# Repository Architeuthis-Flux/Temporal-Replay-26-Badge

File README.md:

# Temporal Badge

Conference badge for Temporal's events. ESP32-S3-MINI-1 (XIAO form factor) with SSD1309
OLED, IR TX/RX for attendee pairing, joystick, tilt switch, and NVS-backed identity.

## Hardware

- **MCU**: ESP32-S3 16r8, dual-core Xtensa LX7, 8 MB flash
- **Display**: SSD1309 128×64 OLED via hardware I2C (SDA=D4/GPIO5, SCL=D5/GPIO6)
- **IR**: NEC protocol TX (D2/GPIO3) + RX (D3/GPIO4)
- **Input**: 4 buttons (D7–D10), analog joystick (D0/D1), tilt switch (D6)

## Prerequisites

- Python 3.9+
- All other dependencies (PlatformIO, Temporal CLI, esptool) are installed by `ignition/setup.sh`

## Build & Flash (Ignition)

```bash
cd ignition
./setup.sh        # first time only — installs all dependencies
./start.sh        # build + flash all connected badges
./start.sh --build-and-flash  # explicit build + fresh filesystem + flash
./start.sh -y     # skip the pre-flash Enter prompt for a ready batch
```

Ignition treats each run as one connected hub batch. Temporal starts a parent
`FlashBadgesWorkflow` plus one human-readable `BadgeFlashWorkflow` child per
detected badge, so the UI shows per-badge flash/WiFi progress and results.

See [`ignition/README.md`](ignition/README.md) for full usage, including `--no-build`, `--build-only`, and `--firmware-dir` options.

## Build (Firmware)

```bash
cd firmware

# Echo badge (default)
./build.sh

# Charlie board
./build.sh charlie

# Non-interactive build (skip build-time network prompt)
./build.sh echo -n
```

Or directly via PlatformIO:
```bash
pio run -e echo
pio run -e charlie
```
Direct PlatformIO builds read `firmware/wifi.local.env` or `BADGE_*`
environment variables and fail if WiFi credentials or the server URL are
missing.

### Dev menu build

Normal firmware hides internal debug/test screens. To flash an Echo badge with
the dev menu enabled for diagnostics and badge-info editing:

```bash
cd firmware
pio run -e echo-dev -t upload --upload-port /dev/cu.usbmodem1101
```

`echo-dev` still uses the configured boop API; it only changes menu/debug
visibility. Use a local settings/server override if you need to avoid staging.

Normal firmware boots straight into the badge menu. Production builds show
Boop, Messages, Contacts, New Msg, Settings, and QR / Pair only while the
badge is unpaired; debug/test screens stay behind the dev menu build.

### MicroPython apps

MicroPython app source lives in `firmware/initial_filesystem/apps/` and is
embedded into firmware builds through `firmware/scripts/generate_startup_files.py`.
Use folder apps with a `main.py` entry point for anything larger than a demo.

Normal firmware does not show the generic Apps menu. Attendee-facing
MicroPython apps need a native `GUI.cpp` launcher and icon; diagnostics can
stay in the dev-menu Apps browser. See
[`firmware/initial_filesystem/apps/README.md`](firmware/initial_filesystem/apps/README.md)
for the full authoring, validation, and build workflow.

### Serial logging

To capture logs from every connected badge while testing hardware flows:

```bash
cd firmware
~/.platformio/penv/bin/python serial_log.py
```

The logger auto-detects USB serial ports, clears `firmware/logs/` by default,
and writes one log file per badge.

### Two-badge hardware test harness

The planned firmware hardware harness uses Ignition to build/flash two badges,
then drives them over USB serial for physical boop and clean-state tests.
See [`docs/hardware-test-harness.md`](docs/hardware-test-harness.md) and
[`specs/012-hardware-test-harness/tasks.md`](specs/012-hardware-test-harness/tasks.md).

## Power Management

The badge uses a 1000 mAh battery drawing ~10 mA in normal operation (~100 hours).
Power saving is tuned for multi-day conferences where WiFi reconnects (~400 mA
for several seconds) cost more than the deep sleep saves if triggered too often.

| State | Trigger | What happens |
|-------|---------|--------------|
| **Active** | Motion / button press | Full brightness, WiFi connected |
| **Dim** | 5 min no motion | LED matrix dims to brightness 3, WiFi stays connected |
| **Deep sleep** | 20 min no motion | 12 μA draw, WiFi disconnects, wakes on IMU motion |
| **Deep sleep (unpaired)** | 5 min no motion | Unpaired badges sleep sooner to save battery in storage |
| **Force sleep** | Hold **UP** button 5 seconds | Immediately enters deep sleep (disabled over USB) |

To wake from deep sleep, move or tilt the badge. After waking, WiFi reconnects
automatically.

## Configuration

Display, input, boop, and timing settings live in `settings.txt` on the
badge's FAT filesystem — no recompile needed. WiFi credentials and the server
URL are build-time secrets and are not written to the badge filesystem.

To configure a badge:
1. Copy `firmware/wifi.local.env.example` to `firmware/wifi.local.env`:
```
BADGE_WIFI_SSID=YourNetwork
BADGE_WIFI_PASS=YourPassword
BADGE_SERVER_URL=https://your-server.example.com
```
2. Build/flash from `firmware/`; the build embeds those values into the firmware.
3. Edit non-secret settings in `settings.txt` as needed:
```
[wifi]
ep_badge = /api/v1/badge
ep_boops = /api/v1/boops
```

`firmware/wifi.local.env` is ignored by git. Environment variables with the
same names override that file for one-off builds. Changing WiFi or backend URL
now requires rebuilding and reflashing the firmware.
Builds require `BADGE_WIFI_SSID`, `BADGE_WIFI_PASS`, and `BADGE_SERVER_URL`;
the badge depends on API connectivity for pairing, messaging, and schedule data.
Badge-facing API calls use MessagePack where supported. Schedule data uses a
compact MessagePack schema and is cached on-device with ETag sidecars. The
schedule app supports `MINE` and `ALL` modes, refreshes in the background on
open, and shows a ticket-page QR for editing an attendee's custom schedule.
Boop and ping list reads also use compact MessagePack arrays; see
[`firmware/src/README.md`](firmware/src/README.md#backend-wire-format) for the
wire contract and measured payload savings.

## Pairing QR

The on-device QR code encodes the badge's compact 12-character machine id,
uppercased for QR alphanumeric mode. The registration scanner uses that id to
attach the physical badge to an attendee record and the badge then fetches the
server-owned identity data.

## Serial Monitor

```bash
cd firmware
pio device monitor --port /dev/cu.usbmodem114101 --baud 115200
```

Or use `./flash.py` (default behavior) to flash and then auto-open monitor logs for one badge.

## Hardware Targets

| Target | Board | Defines file |
|--------|-------|------|
| `delta` | Temporal Badge DELTA (ESP32-S3-MINI-1, XIAO form factor) | `firmware/src/DeltaDefines.h` |
| `charlie` | Jumperless/Charlie board (ESP32-S3-DevKitC-1-N16R8V) | `firmware/src/CharlieDefines.h` |
| `echo` | Echo board production firmware | `firmware/src/EchoDefines.h` |
| `echo-dev` | Echo board with internal dev menu enabled | `firmware/src/EchoDefines.h` |

### Adding a new hardware target

1. Copy `firmware/src/DeltaDefines.h` → `firmware/src/MyBoardDefines.h`
2. Update pin numbers to match your schematic
3. Add `BADGE_HAS_*` flags for any optional peripherals your board has (see `firmware/src/CharlieDefines.h` for the full list)
4. Add a new `[env:myboard]` section to `firmware/platformio.ini` with `-DHARDWARE_MYBOARD`
5. Add `#include "MyBoardDefines.h"` to `firmware/src/HardwareConfig.h`

## Key Source Files

- [firmware/src/main.cpp](firmware/src/main.cpp) — setup() and loop()
- [firmware/src/HardwareConfig.h](firmware/src/HardwareConfig.h) — hardware target selector
- [firmware/src/DeltaDefines.h](firmware/src/DeltaDefines.h) — DELTA pin assignments
- [firmware/src/CharlieDefines.h](firmware/src/CharlieDefines.h) — Charlie pin assignments + feature flags
- [firmware/platformio.ini](firmware/platformio.ini) — build environments

## Repo Structure

| Directory | Contents |
|-----------|----------|
| [`firmware/`](firmware/) | Arduino C++ firmware — active PlatformIO project |
| [`hardware/DELTA/`](hardware/DELTA/) | KiCad PCB — ESP32-S3-MINI-1 XIAO, SSD1309 OLED, IR, buttons |
| [`registrationScanner/`](registrationScanner/) | Quart + Temporal backend (badge enrollment + boop workflows) |
| [`specs/`](specs/) | Feature specs and implementation plans |
| [`assets/`](assets/) | Art and design resources |
| [`docs/`](docs/) | Design notes, photos, work log |

## Legacy Firmware

`firmware/Firmware-0308-modular/` and `firmware/Firmware-0308/` are previous Arduino IDE builds kept for reference. They use a different build system and are not maintained.

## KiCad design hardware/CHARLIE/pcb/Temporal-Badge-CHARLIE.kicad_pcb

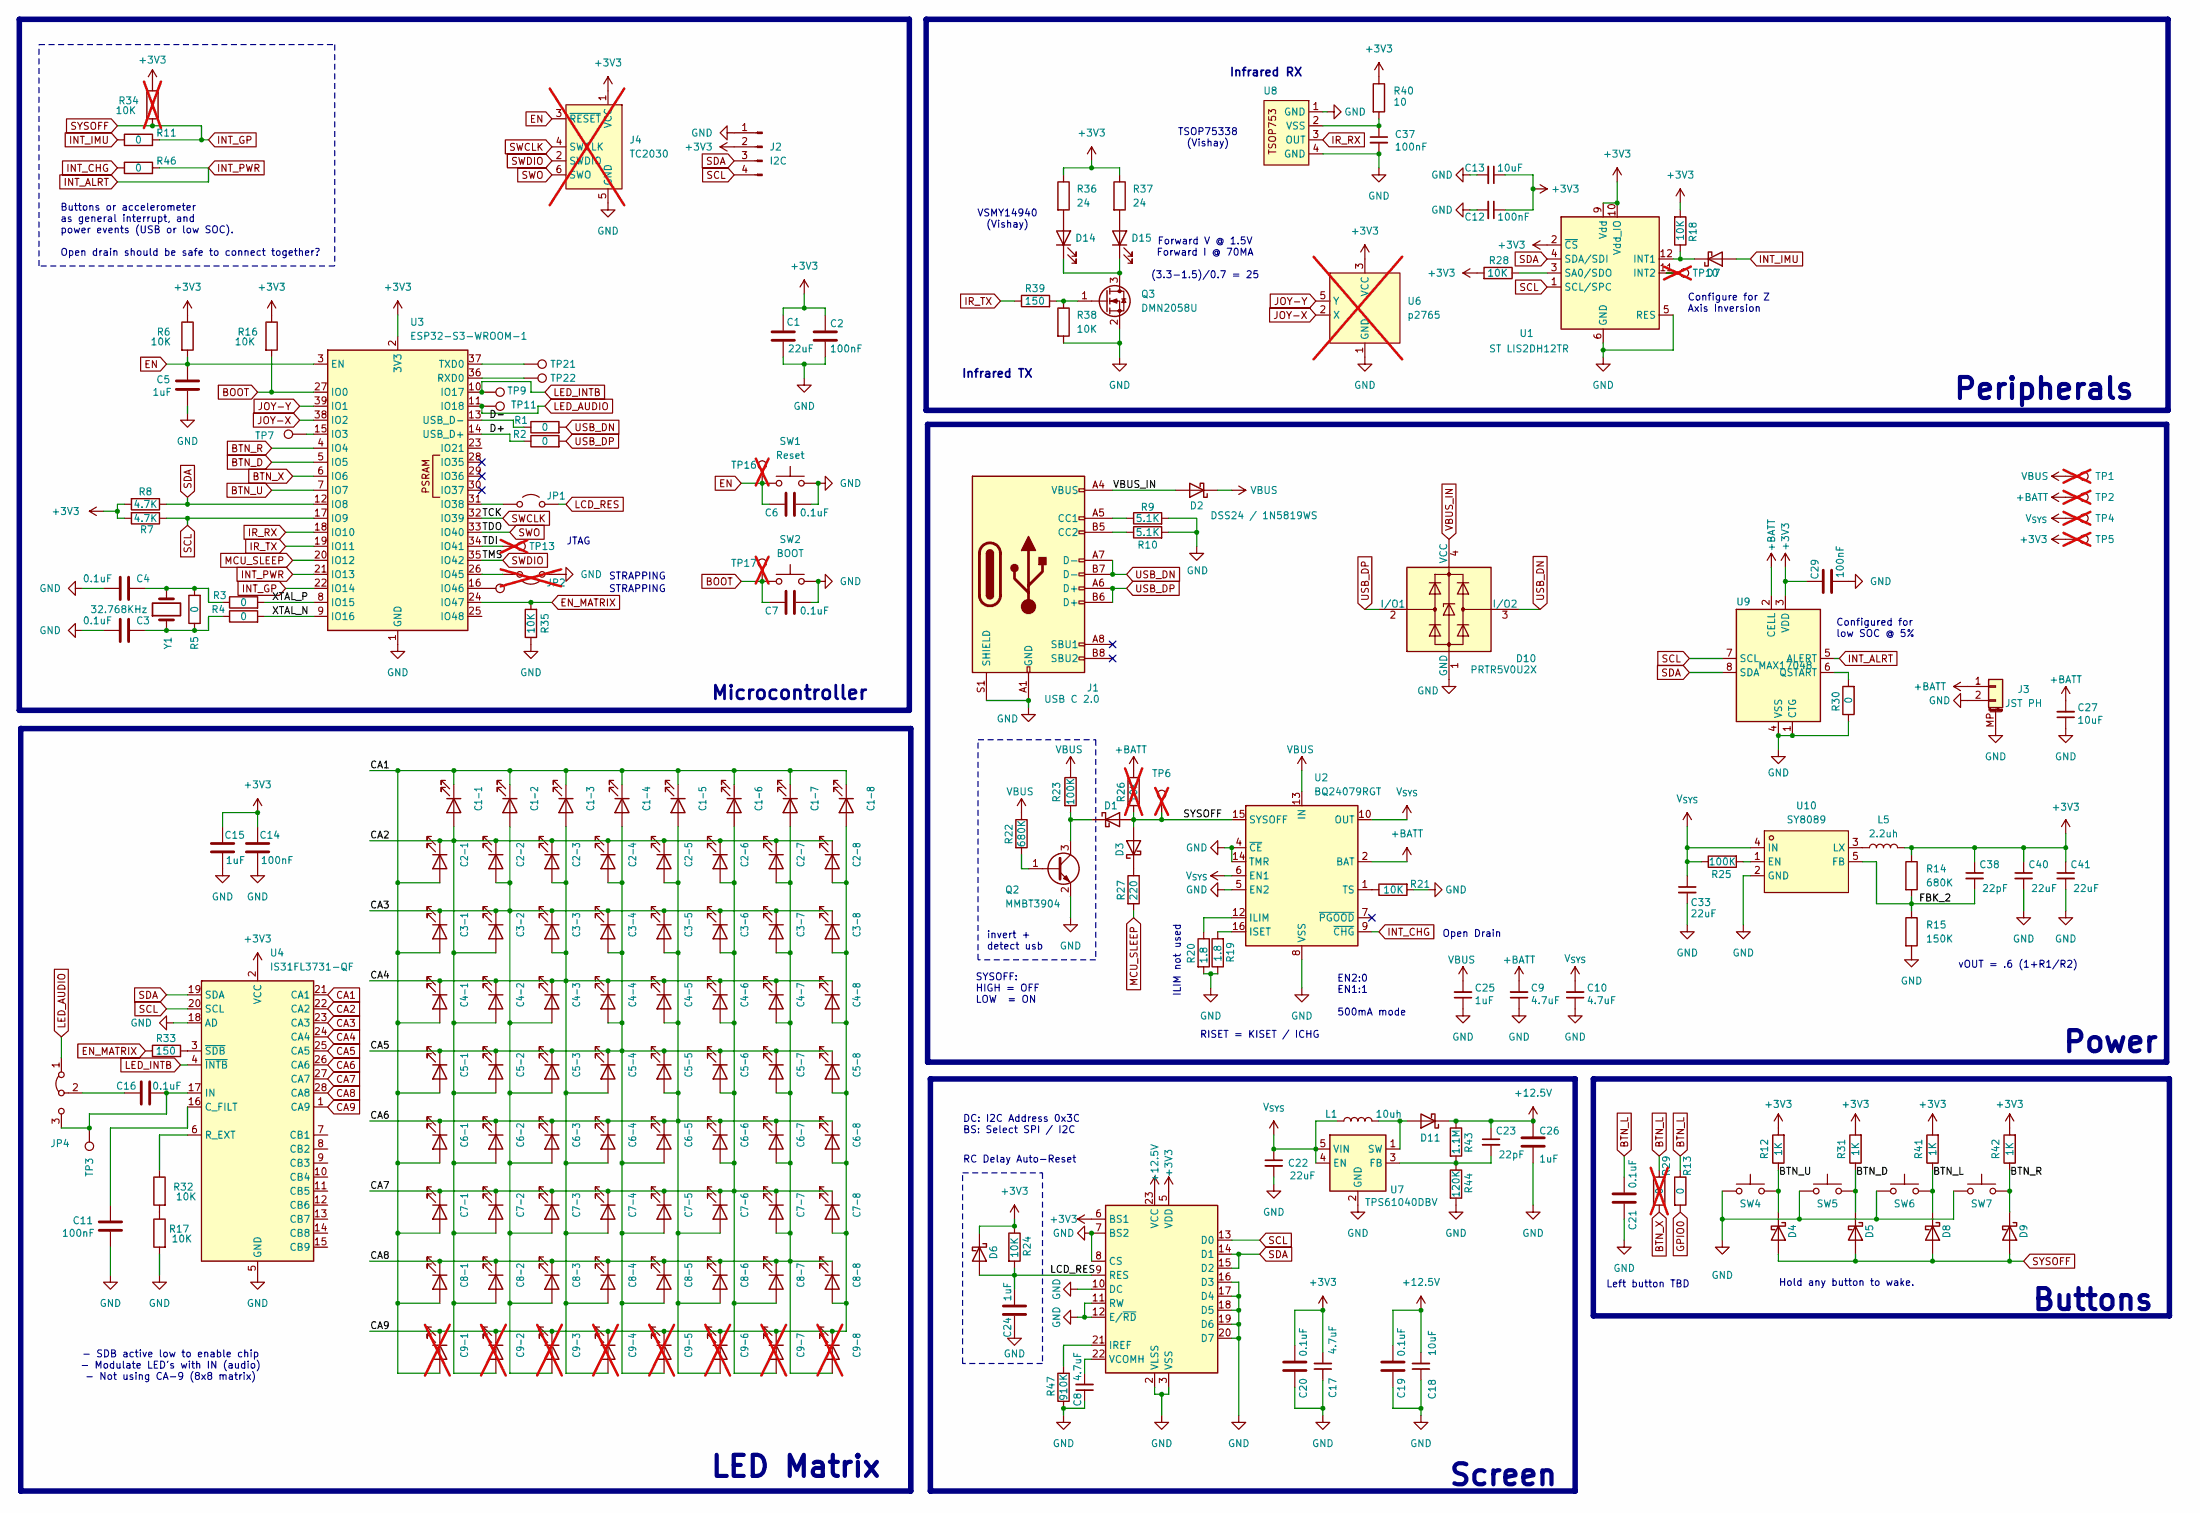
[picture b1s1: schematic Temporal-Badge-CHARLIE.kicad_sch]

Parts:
C1, C22, C33, C40, C41: 22uF; C_0402_1005Metric; LCSC C3845593
C1-1, C1-2, C1-3, C1-4, C1-5, C1-6, C1-7, C1-8, C2-1, C2-2, C2-3, C2-4, C2-5, C2-6, C2-7, C2-8, C3-1, C3-2, C3-3, C3-4, C3-5, C3-6, C3-7, C3-8, C4-1, C4-2, C4-3, C4-4, C4-5, C4-6, C4-7, C4-8, C5-1, C5-2, C5-3, C5-4, C5-5, C5-6, C5-7, C5-8, C6-1, C6-2, C6-3, C6-4, C6-5, C6-6, C6-7, C6-8, C7-1, C7-2, C7-3, C7-4, C7-5, C7-6, C7-7, C7-8, C8-1, C8-2, C8-3, C8-4, C8-5, C8-6, C8-7, C8-8: LED0603_NOOUTLINE; CHIPLED_0603_NOOUTLINE; LCSC C19171390
C2, C11, C12, C14, C29, C37: 100nF; C_0402_1005Metric; LCSC C1525
C3, C4, C6, C7, C16, C19, C20, C21: 0.1uF; C_0402_1005Metric; LCSC C1525
C5, C15, C24, C25: 1uF; C_0402_1005Metric; LCSC C14445
C8, C9, C10, C17: 4.7uF; C_0402_1005Metric; LCSC C315248
C9-1, C9-2, C9-3, C9-4, C9-5, C9-6, C9-7, C9-8: LED0603_NOOUTLINE; CHIPLED_0603_NOOUTLINE; not fitted
C13, C18, C27: 10uF; C_0402_1005Metric; LCSC C315248
C23, C38: 22pF; C_0402_1005Metric; LCSC C76960
C26: 1uF; C_0402_1005Metric; LCSC C1525
D1, D3, D4, D5, D6, D7, D8, D9, D11: D_Schottky; D_SOD-523; LCSC C917006
D2: DSS24 / 1N5819WS; D_SOD-123F; LCSC C511865
D10: PRTR5V0U2X; SOT-143; LCSC C5180302
D14, D15: VSMY14940; vsmy14940; LCSC C511069
J1: USB C 2.0; USB_C_Receptacle_Palconn_UTC16-G; LCSC C2765186
J2: I2C; PinSocket_1x04_P2.54mm_Vertical
J3: JST PH; JST_PH_S2B-PH-SM4-TB_1x02-1MP_P2.00mm_Horizontal; LCSC C295747
J4: TC2030; Tag-Connect_TC2030-IDC-NL_2x03_P1.27mm_Vertical; not fitted
JP1: Jumper_2_Open; SolderJumper-2_P1.3mm_Open_RoundedPad1.0x1.5mm
JP2: Jumper_2_Open; SolderJumper-2_P1.3mm_Open_RoundedPad1.0x1.5mm; not fitted
JP4: Jumper_3_Bridged12; SolderJumper-3_P1.3mm_Bridged12_Pad1.0x1.5mm
L1: 10uh; L_Coilcraft_LPS3010; LCSC C2926400
L5: 2.2uh; L_Coilcraft_LPS3010; LCSC C2926400
Q2: MMBT3904; SOT-23; LCSC C916374
Q3: DMN2058U; SOT-23; LCSC C461001
R1, R2, R3, R4, R5, R11, R13, R30, R46: 0; R_0201_0603Metric; LCSC C106228
R6, R16, R17, R18, R21, R24, R28, R32, R35, R38: 10K; R_0402_1005Metric; LCSC C60490
R7, R8: 4.7K; R_0402_1005Metric; LCSC C105871
R9, R10: 5.1K; R_0402_1005Metric; LCSC C25905
R12, R31, R41, R42: 1K; R_0402_1005Metric; LCSC C106235
R14, R22: 680K; R_0402_1005Metric; LCSC C163456
R15: 150K; R_0402_1005Metric; LCSC C93947
R19, R20: 1.8; R_0402_1005Metric; LCSC C203083
R23, R25: 100K; R_0402_1005Metric; LCSC C60491
R26: 10K; R_0402_1005Metric; LCSC C25767; not fitted
R27: 220; R_0402_1005Metric; LCSC C112291
R29: 0; R_0201_0603Metric; LCSC C106228; not fitted
R33, R39: 150; R_0402_1005Metric; LCSC C138054
R34: 10K; R_0402_1005Metric; LCSC C60490; not fitted
R36, R37: 24; R_0805_2012Metric; LCSC C270625
R40: 10; R_0402_1005Metric; LCSC C138066
R43: 1.1M; R_0402_1005Metric; LCSC C163456
R44: 120K; R_0402_1005Metric; LCSC C93947
R47: 910K; R_0402_1005Metric; LCSC C163456
SW1: Reset; SW_SPST_B3U-1000P-B; LCSC C231329
SW2: BOOT; Panasonic_EVQPUM_EVQPUD; LCSC C79174
SW4, SW5, SW6, SW7: SW_Push; SW_Push_1TS009xxxx-xxxx-xxxx_6x6x5mm; LCSC C25168849
TP1, TP2, TP4, TP5, TP6, TP10, TP13, TP16, TP17: TestPoint; TestPoint_Pad_D1.0mm; not fitted
TP3, TP7, TP8, TP9, TP11, TP21, TP22: TestPoint; TestPoint_Pad_D1.0mm
U1: ST LIS2DH12TR; LGA-12_2x2mm_P0.5mm; LCSC C110926
U2: BQ24079RGT; VQFN-16-1EP_3x3mm_P0.5mm_EP1.6x1.6mm; LCSC C2876751
U3: ESP32-S3-WROOM-1; LCSC C2913202
U4: IS31FL3731-QF; QFN-28-1EP_4x4mm_P0.4mm_EP2.3x2.3mm; LCSC C191206
U5: (no value)
U6: p2765; JOYSTICK_ANALOG_MINITHM; not fitted
U7: TPS61040DBV; SOT-23-5
U8: TSOP75338; TSOP753; LCSC C499550
U9: MAX17048; TDFN-8-1EP_2x2mm_P0.5mm_EP0.8x1.2mm; LCSC C2682616
U10: SY8089; SOT-23-5; LCSC Part C79313
Y1: 32.768KHz; Crystal_SMD_3215-2Pin_3.2x1.5mm; LCSC C97606

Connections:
+3V3: C1.1, C2.1, C12.1, C13.1, C14.1, C15.1, C17.2, C20.2, C29.1, C38.1, C40.1, C41.1, D6.1 (K), J2.2, J4.1 (VCC), L5.2, R6.1, R7.2, R8.2, R12.2, R14.1, R16.1, R18.2, R24.1, R28.2, R31.2, R34.1, R36.1, R37.1, R40.1, R41.2, R42.2, TP5.1, U1.2 (~CS), U1.9 (Vdd), U1.10 (Vdd_IO), U3.2 (3V3), U4.2 (VCC), U5.5 (VDD), U5.6 (BS1), U6.3 (VCC), U6.4 (VCC), U9.3 (VDD)
+12.5V: C18.2, C19.2, C23.1, C26.2, D11.1 (K), R43.1, U5.23 (VCC)
+BATT: C9.2, C27.2, J3.1, R26.1, TP2.1, U2.2 (BAT), U2.3 (BAT), U9.2 (CELL)
/D+: R2.1, U3.14 (USB_D+)
/D-: R1.1, U3.13 (USB_D-)
/FBK_2: C38.2, R14.2, R15.1, U10.5 (FB)
/TDI: TP13.1, U3.34 (IO41)
/XTAL_N: R4.2, U3.9 (IO16)
/XTAL_P: R3.2, U3.8 (IO15)
BOOT: C7.1, R16.2, SW2.2, TP17.1, U3.27 (IO0)
BTN_D: D5.1 (K), R31.1, SW5.2, U3.5 (IO5)
BTN_L: C21.2, D8.1 (K), R13.1, R29.1, R41.1, SW6.2
BTN_R: D9.1 (K), R42.1, SW7.2, U3.4 (IO4)
BTN_U: D4.1 (K), R12.1, SW4.2, U3.7 (IO7)
BTN_X: R29.2, U3.6 (IO6)
CA1: C1-1.1 (K), C1-2.1 (K), C1-3.1 (K), C1-4.1 (K), C1-5.1 (K), C1-6.1 (K), C1-7.1 (K), C1-8.1 (K), C2-1.2 (A), C3-1.2 (A), C4-1.2 (A), C5-1.2 (A), C6-1.2 (A), C7-1.2 (A), C8-1.2 (A), C9-1.2 (A), U4.21 (CA1)
CA2: C1-1.2 (A), C2-1.1 (K), C2-2.1 (K), C2-3.1 (K), C2-4.1 (K), C2-5.1 (K), C2-6.1 (K), C2-7.1 (K), C2-8.1 (K), C3-2.2 (A), C4-2.2 (A), C5-2.2 (A), C6-2.2 (A), C7-2.2 (A), C8-2.2 (A), C9-2.2 (A), U4.22 (CA2)
CA3: C1-2.2 (A), C2-2.2 (A), C3-1.1 (K), C3-2.1 (K), C3-3.1 (K), C3-4.1 (K), C3-5.1 (K), C3-6.1 (K), C3-7.1 (K), C3-8.1 (K), C4-3.2 (A), C5-3.2 (A), C6-3.2 (A), C7-3.2 (A), C8-3.2 (A), C9-3.2 (A), U4.23 (CA3)
CA4: C1-3.2 (A), C2-3.2 (A), C3-3.2 (A), C4-1.1 (K), C4-2.1 (K), C4-3.1 (K), C4-4.1 (K), C4-5.1 (K), C4-6.1 (K), C4-7.1 (K), C4-8.1 (K), C5-4.2 (A), C6-4.2 (A), C7-4.2 (A), C8-4.2 (A), C9-4.2 (A), U4.24 (CA4)
CA5: C1-4.2 (A), C2-4.2 (A), C3-4.2 (A), C4-4.2 (A), C5-1.1 (K), C5-2.1 (K), C5-3.1 (K), C5-4.1 (K), C5-5.1 (K), C5-6.1 (K), C5-7.1 (K), C5-8.1 (K), C6-5.2 (A), C7-5.2 (A), C8-5.2 (A), C9-5.2 (A), U4.25 (CA5)
CA6: C1-5.2 (A), C2-5.2 (A), C3-5.2 (A), C4-5.2 (A), C5-5.2 (A), C6-1.1 (K), C6-2.1 (K), C6-3.1 (K), C6-4.1 (K), C6-5.1 (K), C6-6.1 (K), C6-7.1 (K), C6-8.1 (K), C7-6.2 (A), C8-6.2 (A), C9-6.2 (A), U4.26 (CA6)
CA7: C1-6.2 (A), C2-6.2 (A), C3-6.2 (A), C4-6.2 (A), C5-6.2 (A), C6-6.2 (A), C7-1.1 (K), C7-2.1 (K), C7-3.1 (K), C7-4.1 (K), C7-5.1 (K), C7-6.1 (K), C7-7.1 (K), C7-8.1 (K), C8-7.2 (A), C9-7.2 (A), U4.27 (CA7)
CA8: C1-7.2 (A), C2-7.2 (A), C3-7.2 (A), C4-7.2 (A), C5-7.2 (A), C6-7.2 (A), C7-7.2 (A), C8-1.1 (K), C8-2.1 (K), C8-3.1 (K), C8-4.1 (K), C8-5.1 (K), C8-6.1 (K), C8-7.1 (K), C8-8.1 (K), C9-8.2 (A), U4.28 (CA8)
CA9: C1-8.2 (A), C2-8.2 (A), C3-8.2 (A), C4-8.2 (A), C5-8.2 (A), C6-8.2 (A), C7-8.2 (A), C8-8.2 (A), C9-1.1 (K), C9-2.1 (K), C9-3.1 (K), C9-4.1 (K), C9-5.1 (K), C9-6.1 (K), C9-7.1 (K), C9-8.1 (K), U4.1 (CA9)
EN: C5.1, C6.1, J4.3 (~RESET), R6.2, SW1.2, TP16.1, U3.3 (EN)
EN_MATRIX: R33.1, R35.2, U3.24 (IO47)
GND: C1.2, C2.2, C3.2, C4.2, C5.2, C6.2, C7.2, C8.1, C9.1, C10.1, C11.2, C12.2, C13.2, C14.2, C15.2, C17.1, C18.1, C19.1, C20.1, C21.1, C22.2, C24.2, C25.1, C26.1, C27.1, C29.2, C33.2, C37.2, C40.2, C41.2, D10.1 (GND), J1.A1 (GND), J1.A12 (GND), J1.B1 (GND), J1.B12 (GND), J1.S1 (SHIELD), J2.1, J3.2, J3.MP (MountPin), J4.5 (GND), JP2.2 (B), Q2.2 (E), Q3.2 (S), R9.2, R10.2, R15.2, R17.2, R19.1, R20.2, R21.2, R30.1, R35.1, R38.2, R44.2, R47.1, SW1.1, SW2.1, SW4.1, SW5.1, SW6.1, SW7.1, U1.5 (RES), U1.6 (GND), U1.7 (GND), U1.8 (GND), U2.4 (~CE), U2.5 (EN2), U2.8 (VSS), U2.14 (TMR), U2.17 (VSS), U3.1 (GND), U3.40 (GND), U3.41 (GND), U4.5 (GND), U4.18 (AD), U4.29 (GND), U5.1 (NC), U5.2 (VLSS), U5.3 (VSS), U5.4 (NC), U5.7 (BS2), U5.8 (CS), U5.10 (DC), U5.11 (RW), U5.12 (E/~RD), U5.16 (D3), U5.17 (D4), U5.18 (D5), U5.19 (D6), U5.20 (D7), U5.24 (NC), U6.1 (GND), U6.6 (GND), U7.2 (GND), U8.1 (GND), U8.4 (GND), U9.1 (CTG), U9.4 (VSS), U9.9 (VSS), U10.2 (GND)
GPIO0: R13.2
INT_ALRT: R46.2, U3.21 (IO13), U9.5 (ALERT)
INT_CHG: R46.1, U2.9 (~CHG)
INT_GP: D1.2 (A), D3.2 (A), D4.2 (A), D5.2 (A), D8.2 (A), D9.2 (A), R11.2, R26.2, R34.2, TP6.1, U2.15 (SYSOFF), U3.22 (IO14)
INT_IMU: D7.2 (A), R11.1
IR_RX: U3.18 (IO10), U8.3 (OUT)
IR_TX: R39.1, U3.19 (IO11)
JOY-X: U3.38 (IO2), U6.2 (X)
JOY-Y: U3.39 (IO1), U6.5 (Y)
LCD_RES: C24.1, D6.2 (A), JP1.2 (B), R24.2, U5.9 (RES)
LED_AUDIO: JP4.1 (A), TP11.1, U3.11 (IO18)
LED_INTB: TP9.1, U3.10 (IO17), U4.4 (~INTB)
MCU_SLEEP: R27.2, U3.20 (IO12)
unnamed: C3.1, R4.1, R5.1, Y1.1
unnamed: C4.1, R3.1, R5.2, Y1.2
unnamed: D1.1 (K), Q2.3 (C), R23.2
unnamed: D3.1 (K), R27.1
unnamed: D7.1 (K), R18.1, U1.12 (INT1)
unnamed: D11.2 (A), L1.2, U7.1 (SW)
unnamed: D14.2 (A), R36.2
unnamed: D14.1 (K), D15.1 (K), Q3.3 (D)
unnamed: D15.2 (A), R37.2
unnamed: J1.A5 (CC1), R9.1
unnamed: J1.B5 (CC2), R10.1
unnamed: JP1.1 (A), U3.31 (IO38)
unnamed: JP2.1 (A), U3.26 (IO45)
unnamed: C16.2, JP4.3 (B), TP3.1, U4.17 (IN)
unnamed: C16.1, JP4.2 (C)
unnamed: Q2.1 (B), R22.2
unnamed: Q3.1 (G), R38.1, R39.2
unnamed: R17.1, R32.2
unnamed: TP10.1, U1.11 (INT2)
unnamed: R28.1, U1.3 (SA0/SDO)
unnamed: R20.1, U2.12 (ILIM)
unnamed: R19.2, U2.16 (ISET)
unnamed: R21.1, U2.1 (TS)
unnamed: TP7.1, U3.15 (IO3)
unnamed: TP8.1, U3.16 (IO46)
unnamed: TP22.1, U3.36 (RXD0)
unnamed: TP21.1, U3.37 (TXD0)
unnamed: C11.1, U4.16 (C_FILT)
unnamed: R32.1, U4.6 (R_EXT)
unnamed: R33.2, U4.3 (~SDB)
unnamed: R47.2, U5.21 (IREF)
unnamed: C8.2, U5.22 (VCOMH)
unnamed: C23.2, R43.2, R44.1, U7.3 (FB)
unnamed: C37.1, R40.2, U8.2 (VSS)
unnamed: R30.2, U9.6 (QSTART)
unnamed: R25.2, U10.1 (EN)
unnamed: L5.1, U10.3 (LX)
SCL: J2.4, R7.1, U1.1 (SCL/SPC), U3.17 (IO9), U4.20 (SCL), U5.13 (D0), U9.7 (SCL)
SDA: J2.3, R8.1, U1.4 (SDA/SDI), U3.12 (IO8), U4.19 (SDA), U5.14 (D1), U5.15 (D2), U9.8 (SDA)
SWCLK: J4.4 (SWCLK), U3.32 (IO39)
SWDIO: J4.2 (SWDIO), U3.35 (IO42)
SWO: J4.6 (SWO), U3.33 (IO40)
USB_DN: D10.3 (I/O2), J1.A7 (D-), J1.B7 (D-), R1.2
USB_DP: D10.2 (I/O1), J1.A6 (D+), J1.B6 (D+), R2.2
VBUS: C25.2, D2.1 (K), R22.1, R23.1, TP1.1, U2.13 (IN)
VBUS_IN: D2.2 (A), D10.4 (VCC), J1.A4 (VBUS), J1.A9 (VBUS), J1.B4 (VBUS), J1.B9 (VBUS)
V_{SYS}: C10.2, C22.1, C33.1, L1.1, R25.1, TP4.1, U2.6 (EN1), U2.10 (OUT), U2.11 (OUT), U7.4 (EN), U7.5 (VIN), U10.4 (IN)

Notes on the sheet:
Power
Buttons or accelerometer as general interrupt, and power events (USB or low SOC). Open drain should be safe to connect together?
RISET = KISET / ICHG
SYSOFF: HIGH = OFF LOW = ON
Configure for Z Axis Inversion
EN2:0 EN1:1 500mA mode
DC: I2C Address 0x3C BS: Select SPI / I2C
ILIM not used
Forward V @ 1.5V Forward I @ 70MA (3.3-1.5)/0.7 = 25
LED Matrix
vOUT = .6 (1+R1/R2)
Left button TBD
Microcontroller
Configured for low SOC @ 5%
- SDB active low to enable chip - Modulate LED's with IN (audio) - Not using CA-9 (8x8 matrix)
TSOP75338 (Vishay)
Open Drain
STRAPPING
Infrared TX
RC Delay Auto-Reset
Peripherals
invert + detect usb
JTAG
Buttons
VSMY14940 (Vishay)
Infrared RX
Hold any button to wake.
Screen

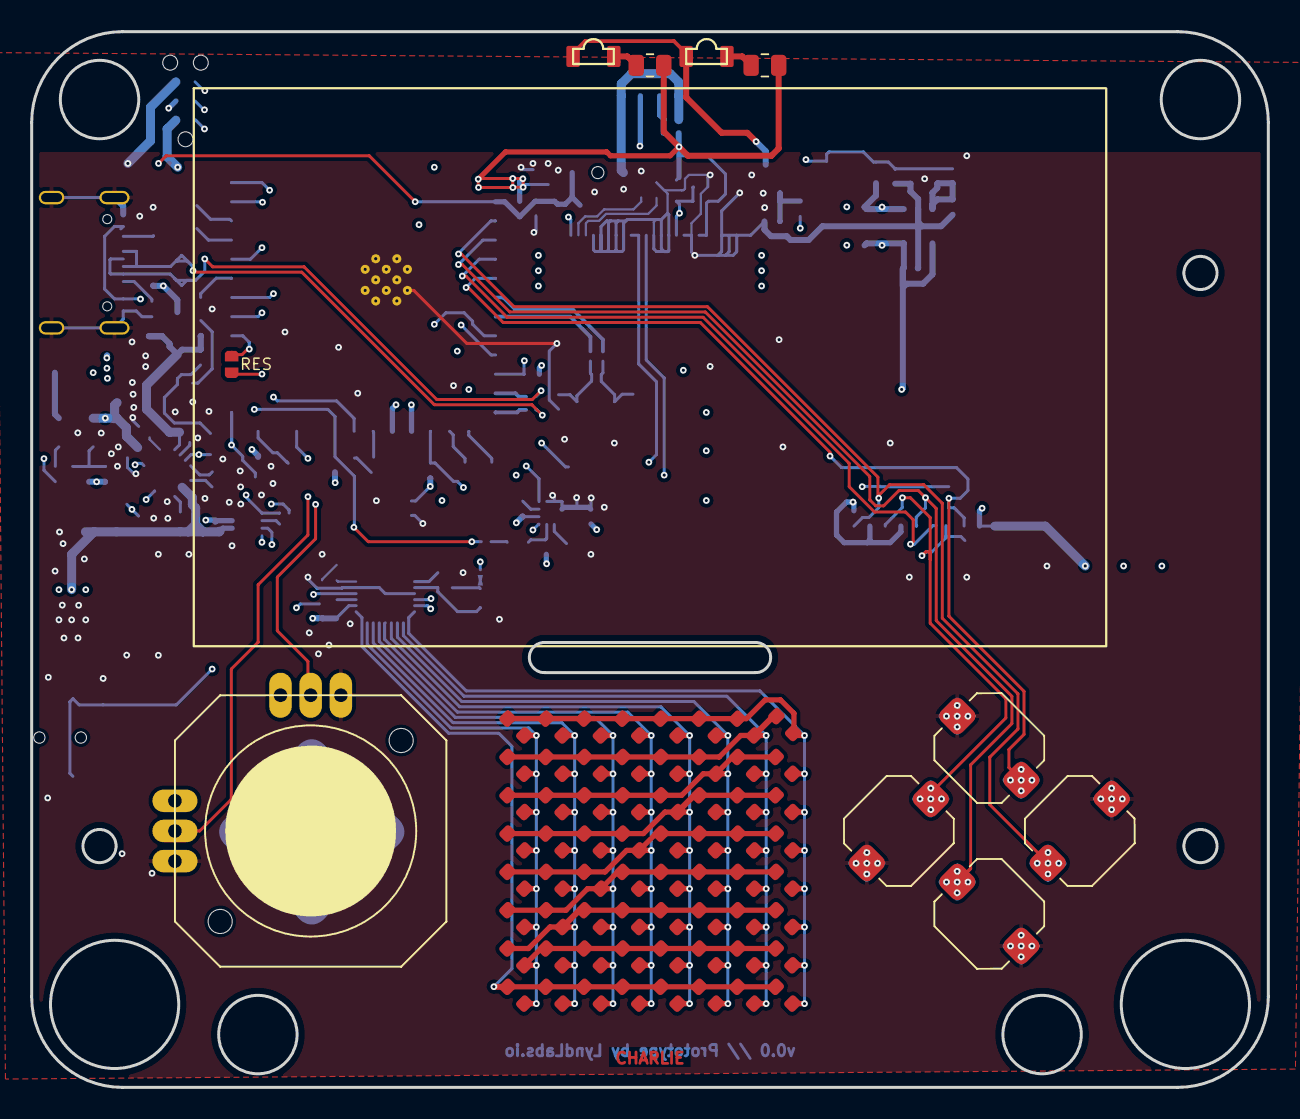
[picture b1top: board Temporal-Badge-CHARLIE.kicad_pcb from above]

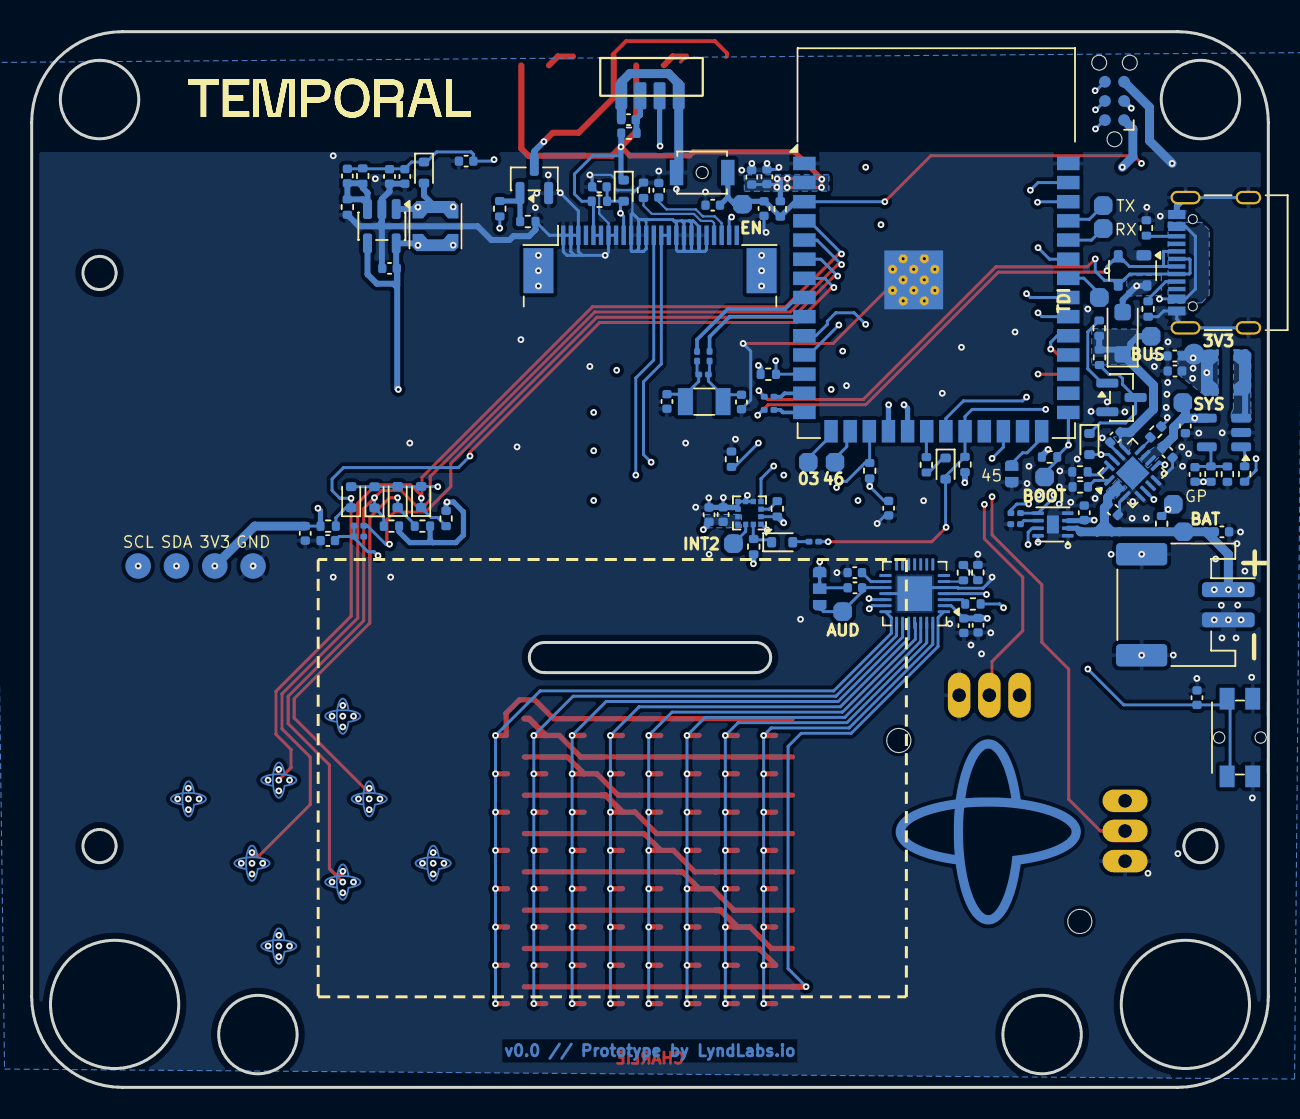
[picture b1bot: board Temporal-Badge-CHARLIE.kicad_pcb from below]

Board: 4 copper layers, 82.0 x 70.0 mm, 198 parts (123 on the bottom side), 86 nets.

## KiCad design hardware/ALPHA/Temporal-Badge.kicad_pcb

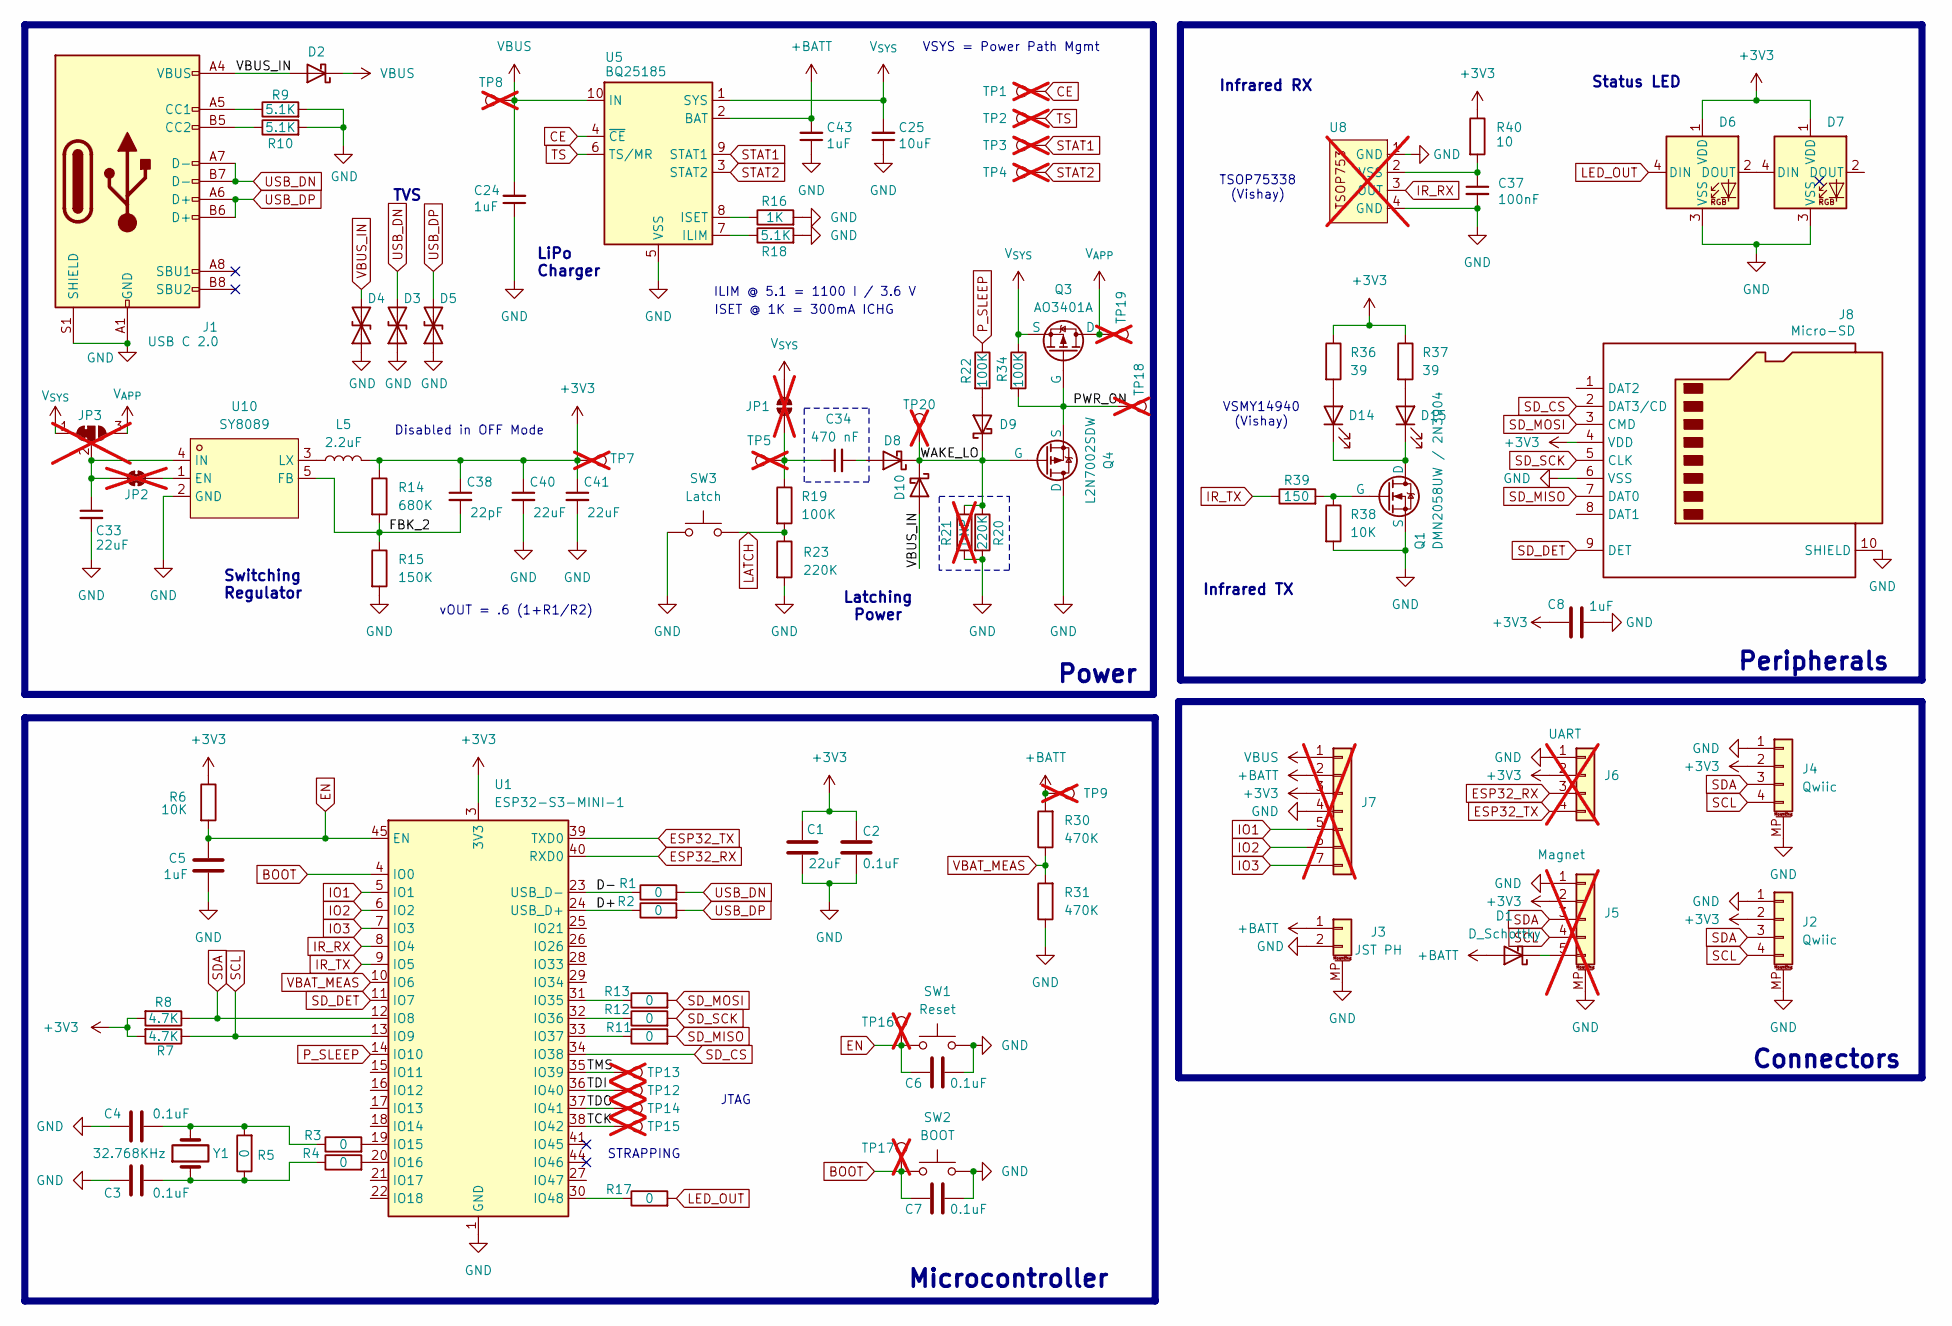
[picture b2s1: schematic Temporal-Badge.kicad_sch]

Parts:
C1, C33, C40, C41: 22uF; C_0402_1005Metric; LCSC C3845593
C2, C3, C4, C6, C7: 0.1uF; C_0402_1005Metric; LCSC C1525
C5, C8, C24, C43: 1uF; C_0402_1005Metric; LCSC C14445
C25: 10uF; C_0402_1005Metric; LCSC C315248
C34: 470 nF; C_0402_1005Metric; LCSC C92361
C37: 100nF; C_0402_1005Metric; LCSC C1525
C38: 22pF; C_0402_1005Metric; LCSC C76960
D1, D2: D_Schottky; D_SOD-323; LCSC C60580
D3, D4, D5: D_TVS; D_SOD-523; LCSC C3008120
D6, D7: WS2812B; LED_WS2812B_PLCC4_5.0x5.0mm_P3.2mm; LCSC C114586
D8, D9, D10: D_Schottky; D_SOD-523; LCSC C917006
D14, D15: VSMY14940; vsmy14940; LCSC C511069
J1: USB C 2.0; USB_C_Receptacle_Palconn_UTC16-G; LCSC C2765186
J2, J4: Qwiic; JST_SH_SM04B-SRSS-TB_1x04-1MP_P1.00mm_Horizontal; LCSC C51940130
J3: JST PH; JST_PH_S2B-PH-SM4-TB_1x02-1MP_P2.00mm_Horizontal; LCSC C295747
J5: Magnet; PinSocket_1x05_P2.54mm_Horizontal; not fitted
J6: UART; PinSocket_1x04_P2.54mm_Vertical; not fitted
J7: Breakout; PinSocket_1x07_P2.54mm_Vertical; not fitted
J8: Micro-SD; MicroSD; LCSC C381082
JP1: SolderJumper_2_Open; SolderJumper-2_P1.3mm_Open_RoundedPad1.0x1.5mm; not fitted
JP2: SolderJumper_2_Bridged; SolderJumper-2_P1.3mm_Bridged_RoundedPad1.0x1.5mm; not fitted
JP3: SolderJumper_3_Bridged12; SolderJumper-3_P1.3mm_Bridged12_RoundedPad1.0x1.5mm; not fitted
L5: 2.2uF; L_Coilcraft_LPS3010; LCSC C2926400
Q1: DMN2058UW / 2N3904; SOT-23; LCSC C54879
Q3: AO3401A; SOT-23; LCSC C15127
Q4: L2N7002SDW; SOT-23; LCSC C383163
R1, R2, R3, R4, R5, R11, R12, R13, R17: 0; R_0402_1005Metric; LCSC C106231
R6, R38: 10K; R_0402_1005Metric; LCSC C60490
R7, R8: 4.7K; R_0402_1005Metric; LCSC C105871
R9, R10, R18: 5.1K; R_0402_1005Metric; LCSC C25905
R14: 680K; R_0402_1005Metric; LCSC C163456
R15: 150K; R_0402_1005Metric; LCSC C93947
R16: 1K; R_0402_1005Metric; LCSC C106235
R19, R22, R34: 100K; R_0402_1005Metric; LCSC C60491
R20, R23: 220K; R_0402_1005Metric; LCSC C25767
R21: DNP; R_0402_1005Metric; not fitted
R30, R31: 470K; R_0402_1005Metric; LCSC C137976
R36, R37: 39; R_0402_1005Metric; LCSC C185420
R39: 150; R_0402_1005Metric; LCSC C138054
R40: 10; R_0402_1005Metric; LCSC C138066
SW1: Reset; Panasonic_EVQPUL_EVQPUC; LCSC C79174
SW2: BOOT; Panasonic_EVQPUL_EVQPUC; LCSC C79174
SW3: Latch; SW_SPST_B3U-1000P-B; LCSC C49234121
TP1, TP2, TP3, TP4, TP5, TP7, TP8, TP9, TP12, TP13, TP14, TP15, TP16, TP17, TP18, TP19, TP20: TestPoint; TestPoint_Pad_D1.0mm; not fitted
U1: ESP32-S3-MINI-1; ESP32-S2-MINI-1; LCSC C3013906
U5: BQ25185; WSON-10-1EP_4x3mm_P0.5mm_EP2.2x2mm; LCSC C19725033
U8: TSOP75338; TSOP753; not fitted
U10: SY8089; SOT-23-5; LCSC Part C79313
Y1: 32.768KHz; Crystal_SMD_3215-2Pin_3.2x1.5mm; LCSC C97606

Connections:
+3V3: C1.1, C2.1, C8.1, C38.1, C40.1, C41.1, D6.1 (VDD), D7.1 (VDD), J2.2, J4.2, J5.2, J6.2, J7.3, J8.4 (VDD), L5.2, R6.1, R7.2, R8.2, R14.1, R36.1, R37.1, R40.1, TP7.1, U1.3 (3V3)
+BATT: C43.2, D1.2 (A), J3.1, J7.2, R30.2, TP9.1, U5.2 (BAT)
/D+: R2.1, U1.24 (USB_D+)
/D-: R1.1, U1.23 (USB_D-)
/FBK_2: C38.2, R14.2, R15.1, U10.5 (FB)
/PWR_ON: Q3.2 (G), Q4.3 (S), R34.2, TP18.1
/TCK: TP15.1, U1.38 (IO42)
/TDI: TP12.1, U1.36 (IO40)
/TDO: TP14.1, U1.37 (IO41)
/TMS: TP13.1, U1.35 (IO39)
/WAKE: D8.1 (K), D9.1 (K), D10.1 (K), Q4.2 (G), R20.1, R21.1, TP20.1
BOOT: C7.1, SW2.2, TP17.1, U1.4 (IO0)
CE: TP1.1, U5.4 (~CE)
EN: C5.1, C6.1, R6.2, SW1.2, TP16.1, U1.45 (EN)
ESP32_RX: J6.3, U1.40 (RXD0)
ESP32_TX: J6.4, U1.39 (TXD0)
GND: C1.2, C2.2, C3.1, C4.1, C5.2, C6.2, C7.2, C8.2, C24.1, C25.1, C33.2, C37.2, C40.2, C41.2, C43.1, D3.1 (A1), D4.1 (A1), D5.1 (A1), D6.3 (VSS), D7.3 (VSS), J1.A1 (GND), J1.A12 (GND), J1.B1 (GND), J1.B12 (GND), J1.S1 (SHIELD), J2.1, J2.MP (MountPin), J3.2, J3.MP (MountPin), J4.1, J4.MP (MountPin), J5.1, J5.MP (MountPin), J6.1, J7.4, J8.6 (VSS), J8.10 (SHIELD), J8.11 (SHIELD), Q1.3 (S), Q4.1 (D), R9.2, R10.2, R15.2, R16.2, R18.2, R20.2, R21.2, R23.2, R31.1, R38.2, SW1.1, SW2.1, SW3.2, U1.1 (GND), U1.2 (GND), U1.42 (GND), U1.43 (GND), U1.46 (GND), U1.47 (GND), U1.48 (GND), U1.49 (GND), U1.50 (GND), U1.51 (GND), U1.52 (GND), U1.53 (GND), U1.54 (GND), U1.55 (GND), U1.56 (GND), U1.57 (GND), U1.58 (GND), U1.59 (GND), U1.60 (GND), U1.61 (GND), U1.62 (GND), U1.63 (GND), U1.64 (GND), U1.65 (GND), U5.5 (VSS), U5.11 (VSS), U8.1 (GND), U8.4 (GND), U10.2 (GND)
IO1: J7.5, U1.5 (IO1)
IO2: J7.6, U1.6 (IO2)
IO3: J7.7, U1.7 (IO3)
IR_RX: U1.8 (IO4), U8.3 (OUT)
IR_TX: R39.1, U1.9 (IO5)
LATCH: R19.2, R23.1, SW3.1
LED_OUT: D6.4 (DIN), R17.2
unnamed: C3.2, R4.1, R5.1, Y1.1
unnamed: C4.2, R3.1, R5.2, Y1.2
unnamed: D1.1 (K), J5.5
unnamed: D6.2 (DOUT), D7.4 (DIN)
unnamed: C34.2, D8.2 (A)
unnamed: D9.2 (A), R22.2
unnamed: D14.2 (A), R36.2
unnamed: D14.1 (K), D15.1 (K), Q1.1 (D)
unnamed: D15.2 (A), R37.2
unnamed: J1.A5 (CC1), R9.1
unnamed: J1.B5 (CC2), R10.1
unnamed: C34.1, JP1.2 (B), R19.1, TP5.1
unnamed: C33.1, JP2.1 (A), JP3.2 (C), U10.4 (IN)
unnamed: JP2.2 (B), U10.1 (EN)
unnamed: Q1.2 (G), R38.1, R39.2
unnamed: R3.2, U1.19 (IO15)
unnamed: R4.2, U1.20 (IO16)
unnamed: R13.1, U1.31 (IO35)
unnamed: R12.1, U1.32 (IO36)
unnamed: R11.1, U1.33 (IO37)
unnamed: R17.1, U1.30 (IO48)
unnamed: R18.1, U5.7 (ILIM)
unnamed: R16.1, U5.8 (ISET)
unnamed: C37.1, R40.2, U8.2 (VSS)
unnamed: L5.1, U10.3 (LX)
P_SLEEP: R22.1, U1.14 (IO10)
SCL: J2.4, J4.4, J5.4, R7.1, U1.13 (IO9)
SDA: J2.3, J4.3, J5.3, R8.1, U1.12 (IO8)
SD_CS: J8.2 (DAT3/CD), U1.34 (IO38)
SD_DET: J8.9 (DET), U1.11 (IO7)
SD_MISO: J8.7 (DAT0), R11.2
SD_MOSI: J8.3 (CMD), R13.2
SD_SCK: J8.5 (CLK), R12.2
STAT1: TP3.1, U5.9 (STAT1)
STAT2: TP4.1, U5.3 (STAT2)
TS: TP2.1, U5.6 (TS/MR)
USB_DN: D3.2 (A2), J1.A7 (D-), J1.B7 (D-), R1.2
USB_DP: D5.2 (A2), J1.A6 (D+), J1.B6 (D+), R2.2
VBAT_MEAS: R30.1, R31.2, U1.10 (IO6)
VBUS: C24.2, D2.1 (K), J7.1, TP8.1, U5.10 (IN)
VBUS_IN: D2.2 (A), D4.2 (A2), D10.2 (A), J1.A4 (VBUS), J1.A9 (VBUS), J1.B4 (VBUS), J1.B9 (VBUS)
V_{APP}: JP3.3 (B), Q3.1 (D), TP19.1
V_{SYS}: C25.2, JP1.1 (A), JP3.1 (A), Q3.3 (S), R34.1, U5.1 (SYS)

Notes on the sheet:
Power
Status LED
ISET @ 1K = 300mA ICHG
VSYS = Power Path Mgmt
vOUT = .6 (1+R1/R2)
Microcontroller
Disabled in OFF Mode
TSOP75338 (Vishay)
ILIM @ 5.1 = 1100 I / 3.6 V
LiPo Charger
Infrared TX
Latching Power
STRAPPING
TVS
Switching Regulator
JTAG
Peripherals
Connectors
VSMY14940 (Vishay)
Infrared RX
